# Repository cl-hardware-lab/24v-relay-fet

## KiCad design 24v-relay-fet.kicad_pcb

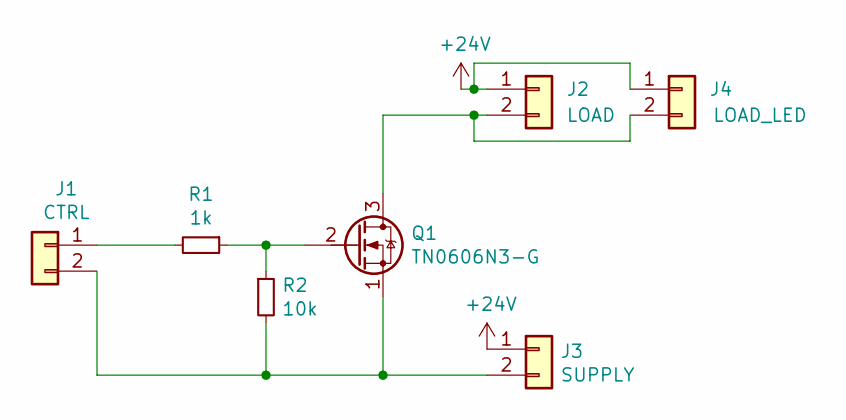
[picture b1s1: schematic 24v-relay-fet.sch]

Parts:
J1: CTRL; PinHeader_1x02_P2.54mm_Vertical
J2: LOAD; JST_XH_S2B-XH-A_1x02_P2.50mm_Horizontal
J3: SUPPLY; JST_XH_S2B-XH-A_1x02_P2.50mm_Horizontal
J4: LOAD_LED; led-connector
Q1: TN0606N3-G; TO-92_HandSolder
R1: 1k; R_0805_2012Metric
R2: 10k; R_0805_2012Metric

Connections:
+24V: J2.1, J3.1, J4.1
unnamed: J1.1, R1.2
unnamed: J1.2, J3.2, Q1.1 (S), R2.2
unnamed: J2.2, J4.2, Q1.3 (D)
unnamed: Q1.2 (G), R1.1, R2.1

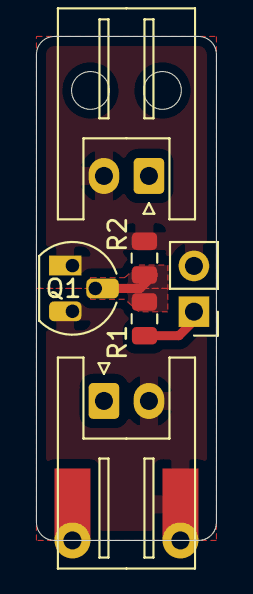
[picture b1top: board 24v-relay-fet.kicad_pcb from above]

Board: 2 copper layers, 10.0 x 28.0 mm, 7 parts (1 on the bottom side), 5 nets.

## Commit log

2021-09-29 Initial Design
